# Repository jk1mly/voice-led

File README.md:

# voice-led

CMOSカウンタICの4017を使ったLED点灯回路の基板
音に反応してクロックが入り点灯するLEDが変わる

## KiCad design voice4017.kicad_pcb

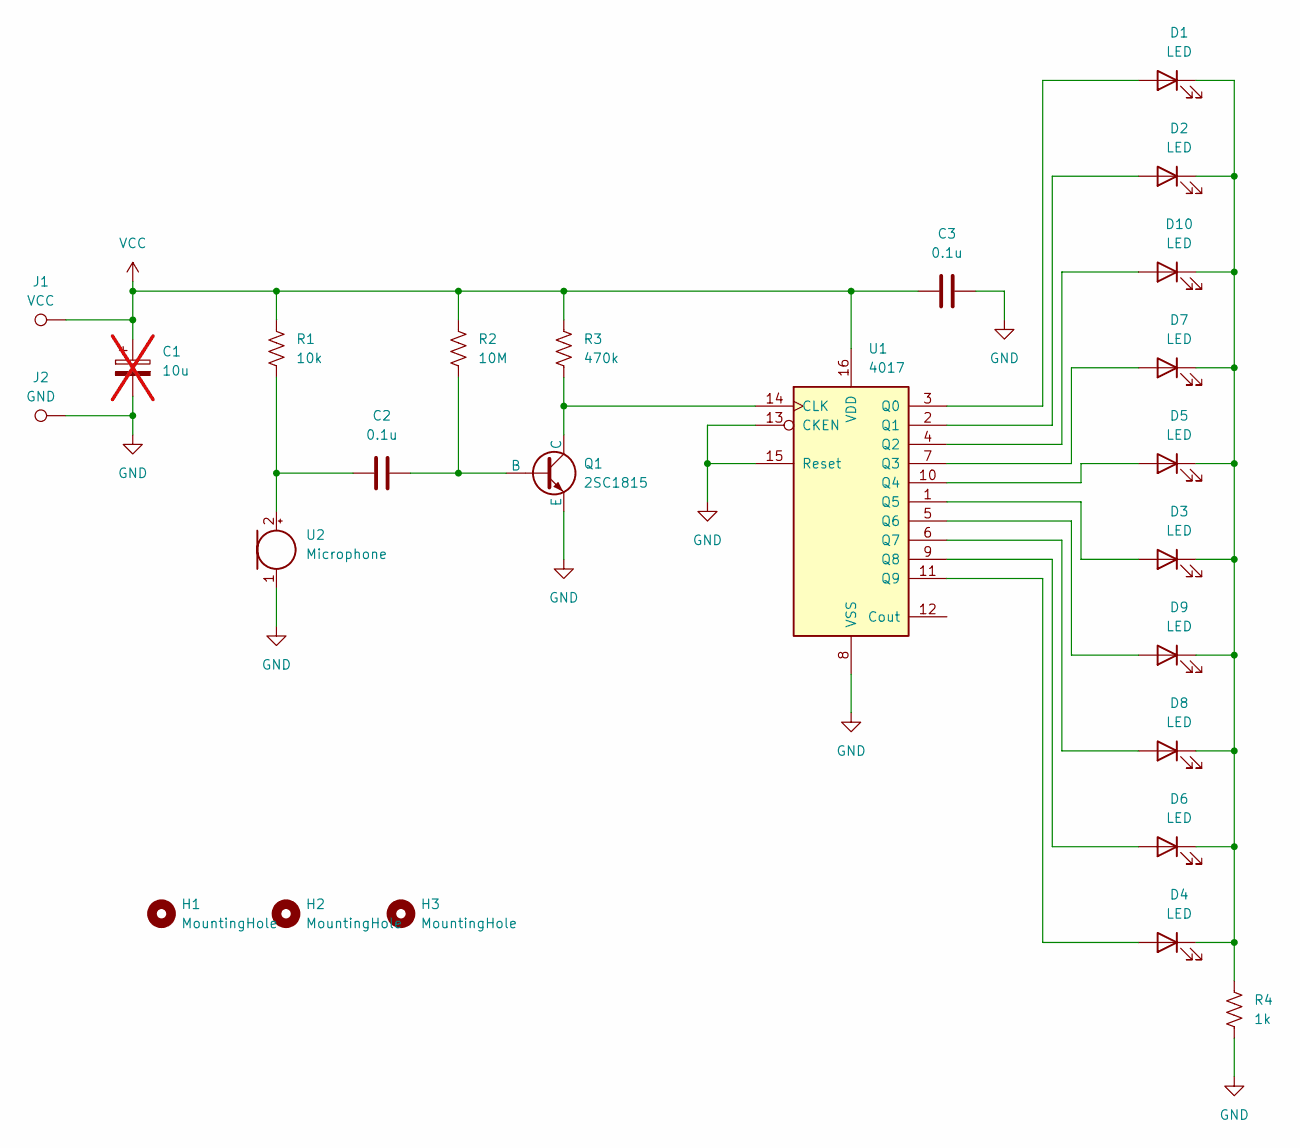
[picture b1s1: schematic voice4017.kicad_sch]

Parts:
C1: 10u; CP_D5.0mm_L11mm_P2.00mm_horiz; not fitted
C2: 0.1u; CP_D5.0mm_L11mm_P2.00mm_horiz
C3: 0.1u; C_Disc_D4.3mm_W1.9mm_P5.00mm
D1, D2, D3, D4, D5, D6, D7, D8, D9, D10: LED; LED_D5.0mm_RS
H1, H2, H3: MountingHole; MountingHole_2.7mm_M2.5
J1: VCC; TestPoint_Loop_D1.80mm_Drill1.0mm_Beaded
J2: GND; TestPoint_Loop_D1.80mm_Drill1.0mm_Beaded
Q1: 2SC1815; TO-92L_Inline_round
R1: 10k; R_Axial_DIN0204_L3.6mm_D1.6mm_P7.62mm_Horizontal
R2: 10M; R_Axial_DIN0204_L3.6mm_D1.6mm_P7.62mm_Horizontal
R3: 470k; R_Axial_DIN0204_L3.6mm_D1.6mm_P7.62mm_Horizontal
R4: 1k; R_Axial_DIN0204_L3.6mm_D1.6mm_P7.62mm_Horizontal
U1: 4017; DIP-16_W7.62mm_Socket_LongPads
U2: Microphone; ECM-D9.7_P2.5

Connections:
GND: C1.2, C3.2, J2.1, Q1.1 (E), R4.2, U1.8 (VSS), U1.13 (CKEN), U1.15 (Reset), U2.1 (-)
unnamed: D1.2 (A), U1.3 (Q0)
unnamed: D1.1 (K), D2.1 (K), D3.1 (K), D4.1 (K), D5.1 (K), D6.1 (K), D7.1 (K), D8.1 (K), D9.1 (K), D10.1 (K), R4.1
unnamed: D2.2 (A), U1.2 (Q1)
unnamed: D3.2 (A), U1.1 (Q5)
unnamed: D4.2 (A), U1.11 (Q9)
unnamed: D5.2 (A), U1.10 (Q4)
unnamed: D6.2 (A), U1.9 (Q8)
unnamed: D7.2 (A), U1.7 (Q3)
unnamed: D8.2 (A), U1.6 (Q7)
unnamed: D9.2 (A), U1.5 (Q6)
unnamed: D10.2 (A), U1.4 (Q2)
unnamed: C2.2, Q1.3 (B), R2.2
unnamed: Q1.2 (C), R3.2, U1.14 (CLK)
unnamed: C2.1, R1.2, U2.2 (+)
VCC: C1.1, C3.1, J1.1, R1.1, R2.1, R3.1, U1.16 (VDD)

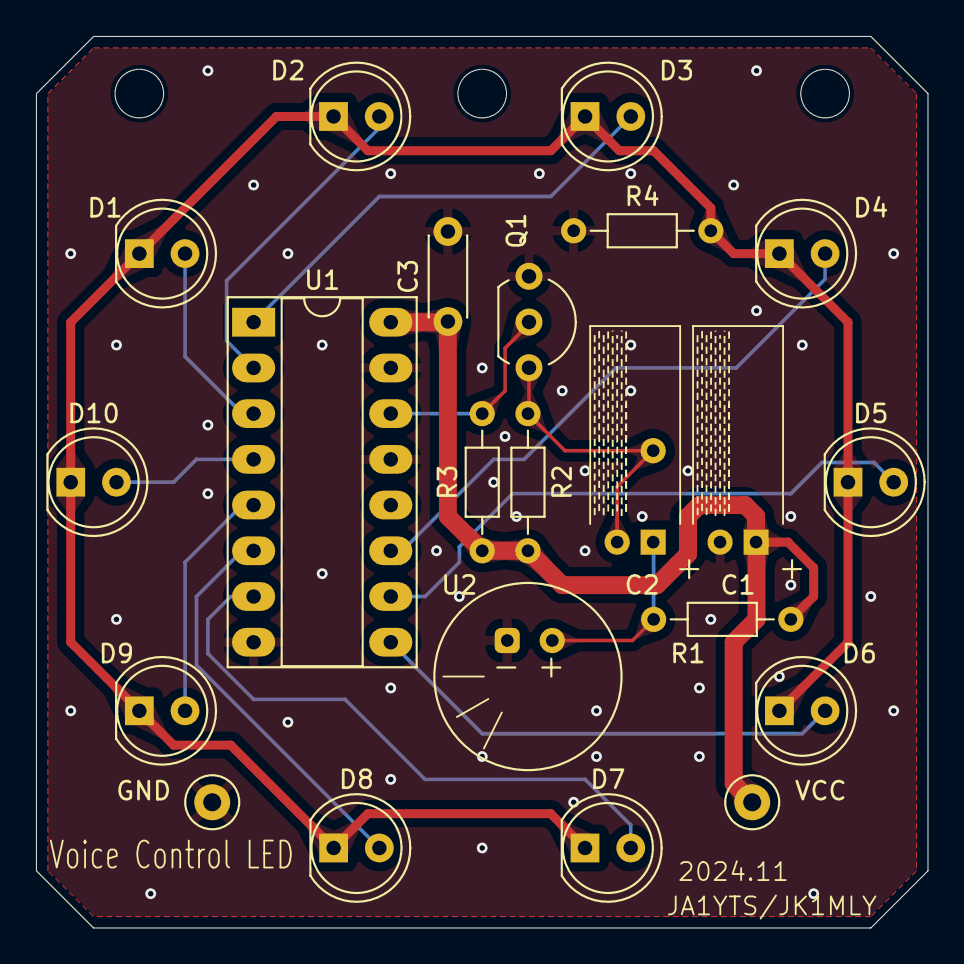
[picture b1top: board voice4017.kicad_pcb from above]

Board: 2 copper layers, 49.5 x 49.5 mm, 25 parts (0 on the bottom side), 16 nets.
